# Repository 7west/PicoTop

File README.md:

# PicoTop

PicoTop is a small computer and operating system built around the RP2350. **This project is a work in progress.** It outputs a black and white terminal over HDMI and takes input from a USB keyboard. It runs its own keyboard-only OS with a shell, text editor, and a small set of programs. "PicoTop" is like laptop, except this one requires you to BYO monitor and keyboard... so not really a laptop at all. I came up with the name before a project pivot.

## Features

- **HDMI out** - 640x480 terminal display over DVI
- **USB keyboard** - standard USB-A keyboard input
- **Rechargeable** - onboard LiPo battery with USB-C charging; battery level visible in the top bar
- **SD card file system** - FAT16 on a micro SD card (FAT16 only; cards must be 2GB or smaller. I have only tested 2GB and 512MB)
- **RTC** - onboard real-time clock keeps time across power cycles
- **Exposed Pins** - 10 female headers expose 3V3, GND, I2C, UART, two GPIO pins, and SWD (to program the RP2350)
- **Vault** - A system to encrypt a 'vault' folder in the file system

## Programs

| Program | Description |
|---|---|
| `shell` | Command-line interface; entry point for all programs and commands |
| `uEdit` | Text editor |
| `calc` | Calculator workbook |
| `hangman` | Hangman game |
| `ptable` | Periodic Table of Elements reference |

### Shell Commands

`history`, `debug-log`, `timeset`, `battv`, `i2ct`, `beep`, `clear`, `ls`, `pwd`, `cd`, `mkdir`, `rmdir`, `rm`, `cp`, `mv`, `sd-format`, `sd-mount`, `sd-unmount`, and GPIO interaction commands. All commands have a `-h` option to describe what they do and how to use them.

## Repo Contents

- HARDWARE/ has the schematics and PCB for the computer and the case .stl files to 3D print the case.
- SOFTWARE/ has all the code. Open that with VS Code and the Pico SDK plugin and build/upload the "shellwork" project.

## Notes

This FAT16 file system does NOT support LFN (Long File Names). It strictly uses 8.3 naming; 8 characters for the file/folder name and 3 for the file/folder extension.

This repository is not used for active development, so everything is in one commit. It will be updated again at the next major milestone.

I am not great at coding, so you will probably find a lot of bad practices and bugs, but I am mostly happy with where the project is right now. I used AI to help write a few snippets and also help with the certain architectures, like for the file system and the text editor.

## More Images

PicoTop in its 3D printed case

Shell program showing the `ls` command. You can see the VAULT/ folder and that all files and folders follow the 8.3 FAT16 naming convention.

uEdit - The simple text editor.

calc - The simple calculator workbook program.

Hangman - so I can say yes to "does it have any games?"

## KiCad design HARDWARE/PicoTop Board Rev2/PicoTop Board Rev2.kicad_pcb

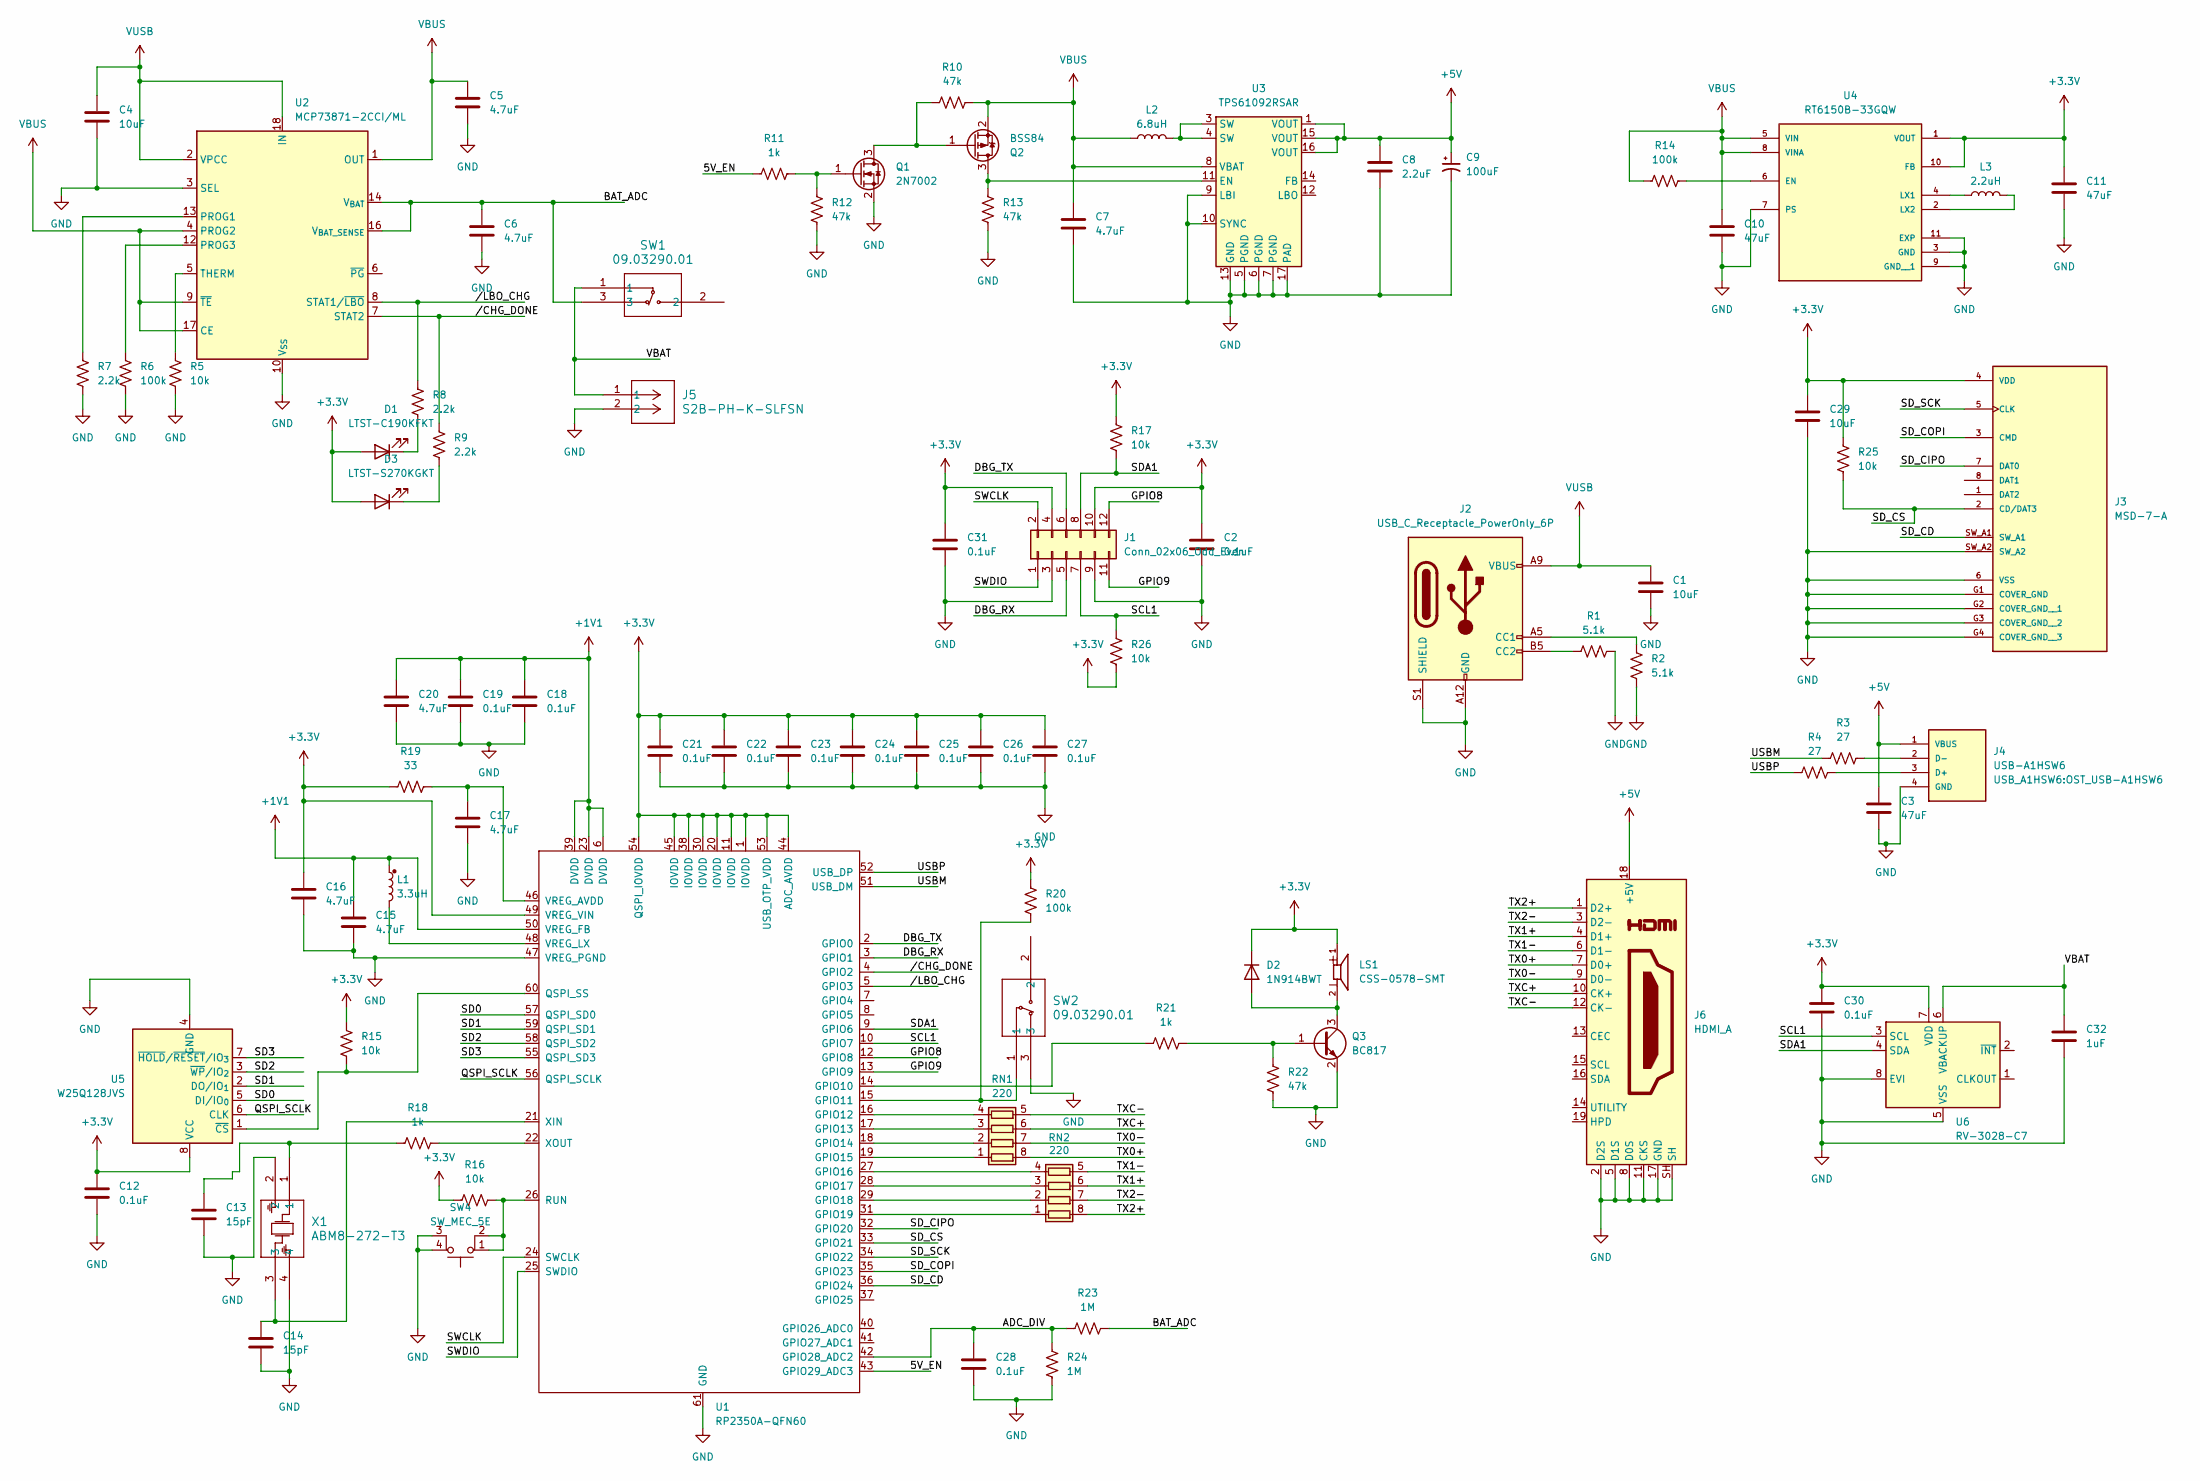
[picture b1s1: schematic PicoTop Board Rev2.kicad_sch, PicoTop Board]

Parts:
C1, C4, C29: 10uF; C_0603_1608Metric
C2, C12, C30, C31: 0.1uF; C_0603_1608Metric
C3, C10, C11: 47uF; C_0603_1608Metric
C5, C6, C7: 4.7uF; C_0603_1608Metric
C8: 2.2uF; C_0603_1608Metric
C9: 100uF; CP_EIA-3216-10_Kemet-I
C13, C14: 15pF; C_0402_1005Metric
C15, C16, C17, C20: 4.7uF; C_0402_1005Metric
C18, C19, C21, C22, C23, C24, C25, C26, C27, C28: 0.1uF; C_0402_1005Metric
C32: 1uF; C_0603_1608Metric
D1: LTST-C190KFKT; LED_0603_1608Metric; MPN LTST-C190KFKT
D2: 1N914BWT; D_SOD-523; MPN 1N914BWT
D3: LTST-S270KGKT; LED_0603_1608Metric; MPN LTST-S270KGKT
J1: Conn_02x06_Odd_Even; PinHeader_2x06_P2.54mm_Vertical
J2: USB_C_Receptacle_PowerOnly_6P; USB_C_Receptacle_GCT_USB4125-xx-x-0190_6P_TopMnt_Horizontal
J3: MSD-7-A; CUI_MSD-7-A; PARTREV 1.0
J4: USB-A1HSW6; OST_USB-A1HSW6; PARTREV A
J5: S2B-PH-K-SLFSN; CONN_S2B-PH-K-S_JST
J6: HDMI_A; HDMI_A_Molex_208658-1001_Horizontal
L1: 3.3uH; L_0805_2012Metric; MPN AOTA-B201610S3R3-101-T
L2: 6.8uH; L_10.4x10.4_H4.8; MPN SRU1028-6R8Y
L3: 2.2uH; L_Coilcraft_LPS3010; MPN VLS3012HBX-2R2M
LS1: CSS-0578-SMT; CUI_CSS-0578-SMT
Q1: 2N7002; SOT-23; MPN 2N7002
Q2: BSS84; SOT-23; MPN BSS84
Q3: BC817; SOT-23-3; MPN BC817-25LT1G
R1, R2: 5.1k; R_0402_1005Metric
R3, R4: 27; R_0402_1005Metric
R5, R15, R16, R17, R25, R26: 10k; R_0402_1005Metric
R6, R14, R20: 100k; R_0402_1005Metric
R7, R8, R9: 2.2k; R_0402_1005Metric
R10, R12, R13, R22: 47k; R_0402_1005Metric
R11, R18, R21: 1k; R_0402_1005Metric
R19: 33; R_0402_1005Metric
R23, R24: 1M; R_0402_1005Metric
RN1, RN2: 220; R_Array_Concave_4x0603
SW1, SW2: 09.03290.01; 09.03290_EAO
SW4: SW_MEC_5E; 7SW_Push_1P1T_NO_CK_KMR2
U1: RP2350A-QFN60; RP2350A_QFN-60_EP_7.75x7.75_Pitch0.4mm; MPN SC1509-A4
U2: MCP73871-2CCI/ML; QFN-20-1EP_4x4mm_P0.5mm_EP2.5x2.5mm; MPN MCP73871-2CCI/ML
U3: TPS61092RSAR; Texas_RSA_VQFN-16-1EP_4x4mm_P0.65mm_EP2.7x2.7mm_ThermalVias; MPN TPS61092RSAR
U4: RT6150B-33GQW; SON50P250X250X80-11N; PARTREV July 2018
U5: W25Q128JVS; SOIC-8_5.3x5.3mm_P1.27mm
U6: RV-3028-C7; MicroCrystal_C7_SON-8_1.5x3.2mm_P0.9mm
X1: ABM8-272-T3; Crystal_SMD_Abracon_ABM8AIG-4Pin_3.2x2.5mm; MPN ABM8-272-T3

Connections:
+1V1: C15.1, C18.1, C19.1, C20.1, L1.1 (PLUS), U1.6 (DVDD), U1.23 (DVDD), U1.39 (DVDD), U1.50 (VREG_FB)
+3.3V: C2.1, C11.1, C12.1, C16.1, C21.1, C22.1, C23.1, C24.1, C25.1, C26.1, C27.1, C29.1, C30.1, C31.1, D1.2 (A), D2.1 (K), D3.2 (A), J1.4, J1.10, J3.4 (VDD), LS1.1, R15.2, R16.2, R17.2, R19.2, R20.2, R25.2, R26.1, U1.1 (IOVDD), U1.11 (IOVDD), U1.20 (IOVDD), U1.30 (IOVDD), U1.38 (IOVDD), U1.44 (ADC_AVDD), U1.45 (IOVDD), U1.49 (VREG_VIN), U1.53 (USB_OTP_VDD), U1.54 (QSPI_IOVDD), U4.1 (VOUT), U4.10 (FB), U5.8 (VCC), U6.7 (VDD)
+5V: C3.2, C8.1, C9.1, J4.1 (VBUS), J6.18 (+5V), U3.1 (VOUT), U3.15 (VOUT), U3.16 (VOUT)
/5V_EN: R11.2, U1.43 (GPIO29_ADC3)
/ADC_DIV: C28.1, R23.2, R24.1, U1.42 (GPIO28_ADC2)
/BAT_ADC: C6.1, R23.1, SW1.3, U2.14 (V_{BAT}), U2.15 (V_{BAT}), U2.16 (V_{BAT_SENSE})
/DBG_RX: J1.5, U1.3 (GPIO1)
/DBG_TX: J1.6, U1.2 (GPIO0)
/GPIO8: J1.12, U1.12 (GPIO8)
/GPIO9: J1.11, U1.13 (GPIO9)
/QSPI_SCLK: U1.56 (QSPI_SCLK), U5.6 (CLK)
/SCL1: J1.7, R26.2, U1.10 (GPIO7), U6.3 (SCL)
/SD0: U1.57 (QSPI_SD0), U5.5 (DI/IO_{0})
/SD1: U1.59 (QSPI_SD1), U5.2 (DO/IO_{1})
/SD2: U1.58 (QSPI_SD2), U5.3 (~WP/IO_{2})
/SD3: U1.55 (QSPI_SD3), U5.7 (~HOLD/~RESET/IO_{3})
/SDA1: J1.8, R17.1, U1.9 (GPIO6), U6.4 (SDA)
/SD_CD: J3.SW_A1, U1.36 (GPIO24)
/SD_CIPO: J3.7 (DAT0), U1.32 (GPIO20)
/SD_COPI: J3.3 (CMD), U1.35 (GPIO23)
/SD_CS: J3.2 (CD/DAT3), R25.1, U1.33 (GPIO21)
/SD_SCK: J3.5 (CLK), U1.34 (GPIO22)
/SWCLK: J1.2, U1.24 (SWCLK)
/SWDIO: J1.1, U1.25 (SWDIO)
/TX0+: J6.7 (D0+), RN1.8 (R1.2)
/TX0-: J6.9 (D0-), RN1.7 (R2.2)
/TX1+: J6.4 (D1+), RN2.6 (R3.2)
/TX1-: J6.6 (D1-), RN2.5 (R4.2)
/TX2+: J6.1 (D2+), RN2.8 (R1.2)
/TX2-: J6.3 (D2-), RN2.7 (R2.2)
/TXC+: J6.10 (CK+), RN1.6 (R3.2)
/TXC-: J6.12 (CK-), RN1.5 (R4.2)
/USBM: R3.2, U1.51 (USB_DM)
/USBP: R4.2, U1.52 (USB_DP)
/VBAT: C32.1, J5.1, SW1.1, U6.6 (VBACKUP)
//CHG_DONE: R9.2, U1.4 (GPIO2), U2.7 (STAT2)
//LBO_CHG: R8.2, U1.5 (GPIO3), U2.8 (STAT1/~LBO)
GND: C1.2, C2.2, C3.1, C4.2, C5.2, C6.2, C7.2, C8.2, C9.2, C10.2, C11.2, C12.2, C13.2, C14.2, C15.2, C16.2, C17.2, C18.2, C19.2, C20.2, C21.2, C22.2, C23.2, C24.2, C25.2, C26.2, C27.2, C28.2, C29.2, C30.2, C31.2, C32.2, J1.3, J1.9, J2.A12 (GND), J2.B12 (GND), J2.S1 (SHIELD), J3.6 (VSS), J3.G1 (COVER_GND), J3.G2 (COVER_GND__1), J3.G3 (COVER_GND__2), J3.G4 (COVER_GND__3), J3.SW_A2, J4.4 (GND), J5.2, J6.2 (D2S), J6.5 (D1S), J6.8 (D0S), J6.11 (CKS), J6.17 (GND), J6.SH, Q1.2 (S), Q3.2 (E), R1.2, R2.1, R5.1, R6.1, R7.1, R12.2, R13.2, R22.2, R24.2, SW2.3, SW4.3 (K), SW4.4 (A), U1.47 (VREG_PGND), U1.61 (GND), U2.3 (SEL), U2.10 (V_{SS}), U2.11 (V_{SS}), U2.21 (V_{SS}), U3.5 (PGND), U3.6 (PGND), U3.7 (PGND), U3.9 (LBI), U3.10 (SYNC), U3.13 (GND), U3.17 (PAD), U4.3 (GND), U4.7 (PS), U4.9 (GND__1), U4.11 (EXP), U5.4 (GND), U6.5 (VSS), U6.8 (EVI), X1.2, X1.4
unnamed: C13.1, R18.2, X1.1
unnamed: D1.1 (K), R8.1
unnamed: D2.2 (A), LS1.2, Q3.3 (C)
unnamed: D3.1 (K), R9.1
unnamed: J2.A5 (CC1), R2.2
unnamed: J2.B5 (CC2), R1.1
unnamed: J4.3 (D+), R4.1
unnamed: J4.2 (D-), R3.1
unnamed: L1.2 (MINUS), U1.48 (VREG_LX)
unnamed: L2.2, U3.3 (SW), U3.4 (SW)
unnamed: Q1.3 (D), Q2.1 (G), R10.2
unnamed: Q1.1 (G), R11.1, R12.1
unnamed: Q2.3 (D), R13.1, U3.11 (EN)
unnamed: Q3.1 (B), R21.1, R22.1
unnamed: RN1.1 (R1.1), U1.19 (GPIO15)
unnamed: RN1.2 (R2.1), U1.18 (GPIO14)
unnamed: RN1.3 (R3.1), U1.17 (GPIO13)
unnamed: RN1.4 (R4.1), U1.16 (GPIO12)
unnamed: RN2.1 (R1.1), U1.31 (GPIO19)
unnamed: RN2.2 (R2.1), U1.29 (GPIO18)
unnamed: RN2.3 (R3.1), U1.28 (GPIO17)
unnamed: RN2.4 (R4.1), U1.27 (GPIO16)
unnamed: R21.2, U1.14 (GPIO10)
unnamed: R20.1, SW2.1, U1.15 (GPIO11)
unnamed: R15.1, U1.60 (QSPI_SS), U5.1 (~CS)
unnamed: R16.1, SW4.1, SW4.2, U1.26 (RUN)
unnamed: C17.1, R19.1, U1.46 (VREG_AVDD)
unnamed: C14.1, U1.21 (XIN), X1.3
unnamed: R18.1, U1.22 (XOUT)
unnamed: R7.2, U2.13 (PROG1)
unnamed: R6.2, U2.12 (PROG3)
unnamed: R5.2, U2.5 (THERM)
unnamed: R14.2, U4.6 (EN)
unnamed: L3.1, U4.4 (LX1)
unnamed: L3.2, U4.2 (LX2)
VBUS: C5.1, C7.1, C10.1, L2.1, Q2.2 (S), R10.1, R14.1, U2.1 (OUT), U2.4 (PROG2), U2.9 (~TE), U2.17 (CE), U2.20 (OUT), U3.8 (VBAT), U4.5 (VIN), U4.8 (VINA)
VUSB: C1.1, C4.1, J2.A9 (VBUS), J2.B9 (VBUS), U2.2 (VPCC), U2.18 (IN), U2.19 (IN)

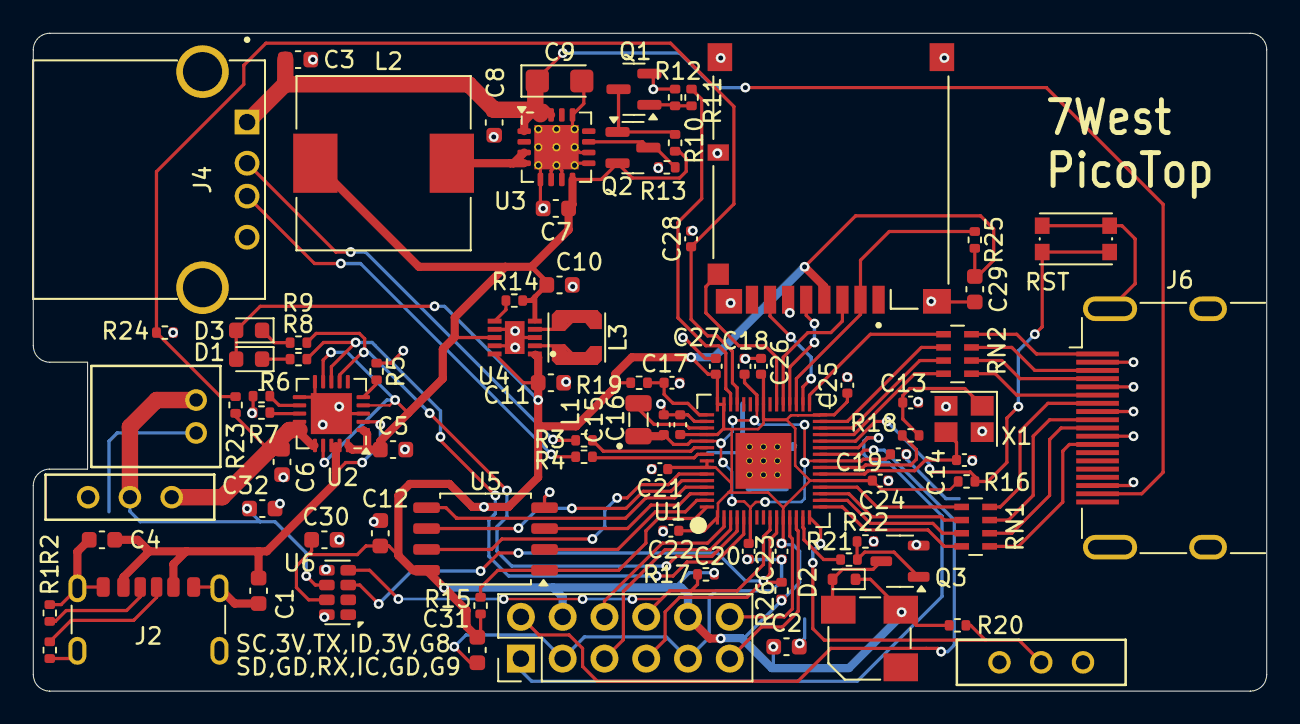
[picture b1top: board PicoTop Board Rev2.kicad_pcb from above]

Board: 2 copper layers, 75.0 x 40.0 mm, 86 parts (0 on the bottom side), 75 nets.

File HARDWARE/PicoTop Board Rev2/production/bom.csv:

Designator,Footprint,Quantity,Value,LCSC Part #
"C1, C29, C4",0603,3,10uF,
"C10, C11, C3",0603,3,47uF,
"C12, C2, C30, C31, C32",0603,5,0.1uF,
"C13, C14",0402,2,15pF,
"C15, C16, C17, C20",0402,4,4.7uF,
"C18, C19, C21, C22, C23, C24, C25, C26, C27, C28",0402,10,0.1uF,
"C5, C6, C7",0603,3,4.7uF,
C8,0603,1,2.2uF,
D2,D_SOD-523,1,1N914BWT,1N914BWT
L1,0805,1,3.3uH,AOTA-B201610S3R3-101-T
Q1,SOT-23,1,2N7002,2N7002
Q2,SOT-23,1,BSS84,BSS84
Q3,SOT-23-3,1,BC817,BC817-25LT1G
"R1, R2",0402,2,5.1k,
"R10, R12, R13, R22",0402,4,47k,
"R11, R18, R21",0402,3,1k,
"R14, R20, R6",0402,3,100k,
"R15, R16, R17, R25, R26, R5, R7",0402,7,10k,
R19,0402,1,33,
"R23, R24",0402,2,1M,
"R3, R4",0402,2,27,
"R8, R9",0402,2,2.2k,
"RN1, RN2",R_Array_Concave_4x0603,2,220,
U1,RP2350A_QFN-60_EP_7.75x7.75_Pitch0.4mm,1,RP2350A-QFN60,SC1509-A4
U2,QFN-20-1EP_4x4mm_P0.5mm_EP2.5x2.5mm,1,MCP73871-2CCI/ML,MCP73871-2CCI/ML
U3,Texas_RSA_VQFN-16-1EP_4x4mm_P0.65mm_EP2.7x2.7mm_ThermalVias,1,TPS61092RSAR,TPS61092RSAR
U5,SOIC-8_5.3x5.3mm_P1.27mm,1,W25Q128JVS,
U6,MicroCrystal_C7_SON-8_1.5x3.2mm_P0.9mm,1,RV-3028-C7,
X1,Crystal_SMD_Abracon_ABM8AIG-4Pin_3.2x2.5mm,1,ABM8-272-T3,ABM8-272-T3

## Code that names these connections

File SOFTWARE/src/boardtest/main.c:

#include <stdio.h>
#include <string.h>

#include "pico/stdlib.h"
#include "hardware/gpio.h"
#include "hardware/adc.h"
#include "hardware/pwm.h"
#include "pico/multicore.h"
#include "pico/sem.h"

#include "terminal.h"
#include "os_debug.h"
#include "usb_kbd.h"
#include "video_out.h"
// #include "rtc.h"
// #include "prog.h"
// #include "shell.h"
#include "fat16.h"
// #include "sd_block.h"

#include "bsp/board.h"
#include "tusb.h"
#include "tusb_config.h"

#define GPIO_5V_EN 29
#define GPIO_CHG_DONE 2
#define GPIO_LBO_CHG 3
#define GPIO_BUZZ_PWM 10
#define GPIO_SLEEP_SWITCH 11
#define GPIO_BATT_ADC 28

/**TODO:
 * GPIO29 - 5V_EN
 * GPIO28/ADC2 - Battery Voltage
 * GPIO2 - /CHG_DONE
 * GPIO3 - /LBO_CHG
 * GPIO8 - button?
 * GPIO10 - Buzzer (PWM5A)
 * GPIO11 - Sleep Switch
 * 
 * DVI:
 * GPIO12
 * GPIO13
 * GPIO14
 * GPIO15
 * GPIO16
 * GPIO17
 * GPIO18
 * GPIO19
 * 
 * SD:
 * GPIO20 - SPI CIPO
 * GPIO21 - SPI CS
 * GPIO22 - SPI SCK
 * GPIO23 - SPI COPI
 * GPIO24 - SPI SD CD
 */


static void core1_main(void) {

    // gpio_init(GPIO_5V_EN);
    // gpio_set_dir(GPIO_5V_EN, GPIO_OUT);
    // gpio_put(GPIO_5V_EN, 1);

    term_init();

    keyboard_init();
    irq_set_enabled(USBCTRL_IRQ, true);
    
    // so DMA always overrules USB, otherwise DVI signal can choke and die
    irq_set_priority(DMA_IRQ_0, 0);
    irq_set_priority(USBCTRL_IRQ, 0xC0);

    gpio_init(GPIO_SLEEP_SWITCH);
    gpio_set_dir(GPIO_SLEEP_SWITCH, GPIO_IN);
    // gpio_pull_up(GPIO_SLEEP_SWITCH);
    gpio_disable_pulls(GPIO_SLEEP_SWITCH);

    gpio_init(GPIO_5V_EN);
    gpio_set_dir(GPIO_5V_EN, GPIO_OUT);
    gpio_put(GPIO_5V_EN, 1);

    bool last_switch_state = true;

    while (1) {

        // printf("Sleep Switch State: %u\n", gpio_get(GPIO_SLEEP_SWITCH));

        if (gpio_get(GPIO_SLEEP_SWITCH) && !last_switch_state) {
            printf("5V off, disp off\n");

            video_out_resume();
            last_switch_state = true;
            gpio_put(GPIO_5V_EN, 1);

        } else if (!gpio_get(GPIO_SLEEP_SWITCH) && last_switch_state) {
            printf("5V on, disp on\n");
            // video_out_pause();
            video_out_setup();
            last_switch_state = false;
            gpio_put(GPIO_5V_EN, 0);

        }

        keyboard_loop_call();

        if (gpio_get(GPIO_SLEEP_SWITCH)) {
            // __wfi(); 
        }

    }
        
}


int main(void) {
    stdio_init_all();

    printf("START\n");

    sleep_ms(2000);

    adc_init();
    adc_gpio_init(GPIO_BATT_ADC);
    adc_select_input(2);

    gpio_set_function(GPIO_BUZZ_PWM, GPIO_FUNC_PWM);
    uint slice_num = pwm_gpio_to_slice_num(GPIO_BUZZ_PWM);
    const uint16_t top = 999;
    pwm_config cfg = pwm_get_default_config();
    pwm_config_set_wrap(&cfg, top);
    pwm_config_set_clkdiv(&cfg, 1.0f);
    pwm_init(slice_num, &cfg, true);

    multicore_launch_core1(core1_main);
    irq_set_enabled(USBCTRL_IRQ, false);

    sleep_ms(2000);
    term_clear_screen();
    term_draw_string(1, 0, "7West");
    term_invert_line(0);

    gpio_init(GPIO_CHG_DONE);
    gpio_set_dir(GPIO_CHG_DONE, GPIO_IN);
    gpio_pull_up(GPIO_CHG_DONE);
    printf("/CHG_DONE: %u\n", gpio_get(GPIO_CHG_DONE));

    gpio_init(GPIO_LBO_CHG);
    gpio_set_dir(GPIO_LBO_CHG, GPIO_IN);
    gpio_pull_up(GPIO_LBO_CHG);
    printf("/LBO_CHG: %u\n", gpio_get(GPIO_LBO_CHG));




    if (fat_mount_sd(true)) {
        printf("FAT Init success\n");
    } else {
        printf("FAT init FAILED\n");
        debug_print_log_UART();
    }
    
    term_set_cursor(0,1);
    
    const float f0 = 1000.0f;
    const float f1 = 2000.0f;
    const int steps = 300;
    const int step_ms = 1;
    while(true) {

        // for (int i = 0; i <= steps; i++) {
        //     float f = f0 + (f1 - f0) * ((float)i / (float)steps);

        //     uint32_t fsys = 150000000;

        //     float div = (float)fsys / (f * (float)(top + 1));
        //     if (div < 1.0f) div = 1.0f;

        //     // pwm_set_clkdiv(slice_num, div);
        //     // pwm_set_gpio_level(GPIO_BUZZ_PWM, (top + 1) / 2);


        //     sleep_ms(step_ms);
        // }

        // sleep_ms(1000);
        



        key_event_t key;
        if (keyboard_queue_pop(&key)) {

            if (key.keycode >= 0) {
                term_putc(key.keycode);
                printf("%c", (char)key.keycode);
                // if (key.keycode == 'f') {
                //     fat_flush();
                // }
            }
        }
        // sleep_ms(2000);

        uint16_t counts = adc_read();
        uint32_t voltage = (165 * counts) >> 10;

        // printf("Raw counts: %u, Voltage*100: %u\n", counts, voltage);


    }
}

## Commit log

2026-04-13 Added all the code
2026-04-13 Reorganized and added hardware files
    Added KiCAD project files and 3D printing files. Reorganized repo into
    hardware & software folders
2026-04-13 Small README.md update
2026-04-13 Added images and updated README
2026-04-13 added some more screenshots
2026-04-29 Fixed several bugs and added new features
    Fixed uEdit bugs (scrolling near the end of files). Added calc features
    (complex numbers, numerical solving, derivatives, and integration).
    Added new periodic table program (ptable). Added new I2C tool (i2ct).
2026-04-29 Updated README for 2 new minor features
2026-06-15 Fixed a few bugs.
